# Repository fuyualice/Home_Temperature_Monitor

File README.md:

# BME280と電子ペーパーを使った自室の環境モニタリングデバイス

## 構成

- Bosh BME280
- Waveshare 4.2inch e-Paper Module
- ESP32-DevKitC-32E

## 仕様

- 10mごとにデータ取得
- データをInfluxDBに送信
- e-Paperの表示更新

- 毎日定時(0:00)にNTPから時刻同期

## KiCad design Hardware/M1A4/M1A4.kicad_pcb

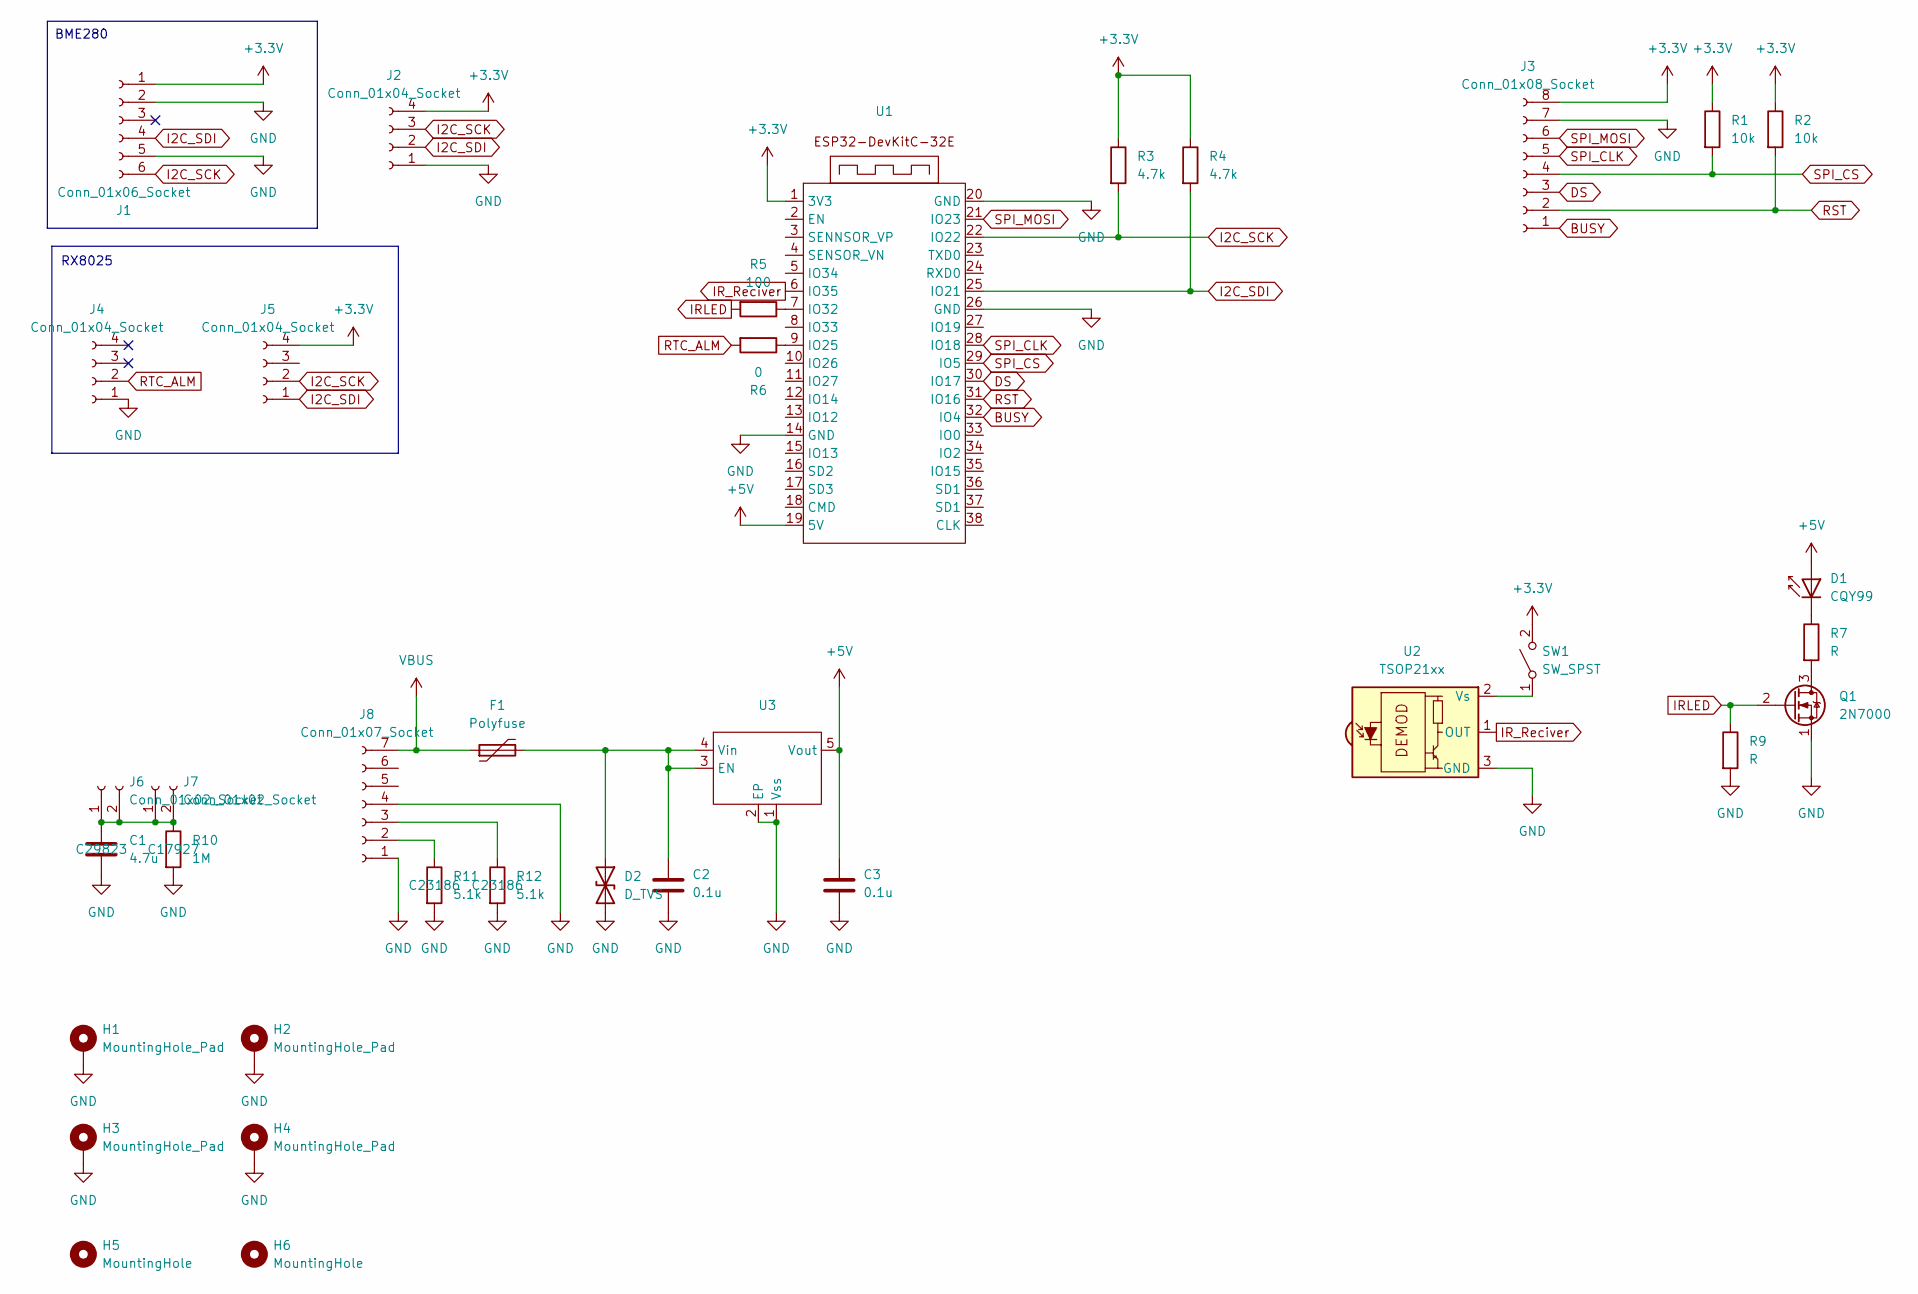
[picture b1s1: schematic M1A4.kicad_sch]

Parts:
C1: 4.7u; C_Disc_D4.3mm_W1.9mm_P5.00mm; LCSC C29823
C2, C3: 0.1u; C_Disc_D4.3mm_W1.9mm_P5.00mm
D1: CQY99; LED_D5.0mm_IRGrey
D2: D_TVS; D_DO-41_SOD81_P7.62mm_Horizontal
F1: Polyfuse; C_Disc_D10.5mm_W5.0mm_P5.00mm
H1, H2, H3, H4: MountingHole_Pad; MountingHole_3.2mm_M3_Pad_Via
H5, H6: MountingHole; MountingHole_3.2mm_M3
J1: Conn_01x06_Socket; PinHeader_1x06_P2.54mm_Vertical
J2: Conn_01x04_Socket; JST_XH_S4B-XH-A-1_1x04_P2.50mm_Horizontal
J3: Conn_01x08_Socket; JST_XH_S8B-XH-A_1x08_P2.50mm_Horizontal
J4, J5: Conn_01x04_Socket; PinHeader_1x04_P2.54mm_Vertical
J6, J7: Conn_01x02_Socket; PinHeader_1x02_P2.54mm_Vertical
J8: Conn_01x07_Socket; PinHeader_1x07_P2.54mm_Vertical
Q1: 2N7000; TO-92_Inline
R1, R2: 10k; R_Axial_DIN0207_L6.3mm_D2.5mm_P10.16mm_Horizontal
R3, R4: 4.7k; R_Axial_DIN0207_L6.3mm_D2.5mm_P10.16mm_Horizontal
R5: 100; R_Axial_DIN0207_L6.3mm_D2.5mm_P10.16mm_Horizontal
R6: 0; R_Axial_DIN0207_L6.3mm_D2.5mm_P10.16mm_Horizontal
R7, R9: R; R_Axial_DIN0207_L6.3mm_D2.5mm_P10.16mm_Horizontal
R10: 1M; R_Axial_DIN0207_L6.3mm_D2.5mm_P10.16mm_Horizontal; LCSC C17927
R11, R12: 5.1k; R_Axial_DIN0204_L3.6mm_D1.6mm_P5.08mm_Horizontal; LCSC C23186
SW1: SW_SPST
U1: esp32-devkit
U2: TSOP21xx; Vishay_MOLD-3Pin
U3: SOT-89-5_Handsoldering

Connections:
+3.3V: J1.1, J2.4, J3.8, J5.4, R1.1, R2.1, R3.1, R4.1, SW1.2 (B), U1.1 (3V3)
+5V: C3.1, D1.2 (A), U1.19 (5V), U3.5 (Vout)
BUSY: J3.1, U1.32 (IO4)
DS: J3.3, U1.30 (IO17)
GND: C1.2, C2.2, C3.2, D2.2 (A2), H1.1, H2.1, H3.1, H4.1, J1.2, J1.5, J2.1, J3.7, J4.1, J8.1, J8.4, Q1.1 (S), R9.2, R10.2, R11.2, R12.2, U1.14 (GND), U1.20 (GND), U1.26 (GND), U2.3 (GND), U3.1 (Vss), U3.2 (EP)
I2C_SCK: J1.6, J2.3, J5.2, R3.2, U1.22 (IO22)
I2C_SDI: J1.4, J2.2, J5.1, R4.2, U1.25 (IO21)
IRLED: Q1.2 (G), R5.2, R9.1
IR_Reciver: U1.6 (IO35), U2.1 (OUT)
unnamed: D1.1 (K), R7.1
unnamed: C2.1, D2.1 (A1), F1.2, U3.3 (EN), U3.4 (Vin)
unnamed: C1.1, J6.1, J6.2, J7.1, J7.2, R10.1
unnamed: J8.2, R11.1
unnamed: J8.3, R12.1
unnamed: Q1.3 (D), R7.2
unnamed: SW1.1 (A), U2.2 (Vs)
unnamed: R6.1, U1.9 (IO25)
unnamed: R5.1, U1.7 (IO32)
RST: J3.2, R2.2, U1.31 (IO16)
RTC_ALM: J4.2, R6.2
SPI_CLK: J3.5, U1.28 (IO18)
SPI_CS: J3.4, R1.2, U1.29 (IO5)
SPI_MOSI: J3.6, U1.21 (IO23)
VBUS: F1.1, J8.7

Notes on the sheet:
RX8025
BME280

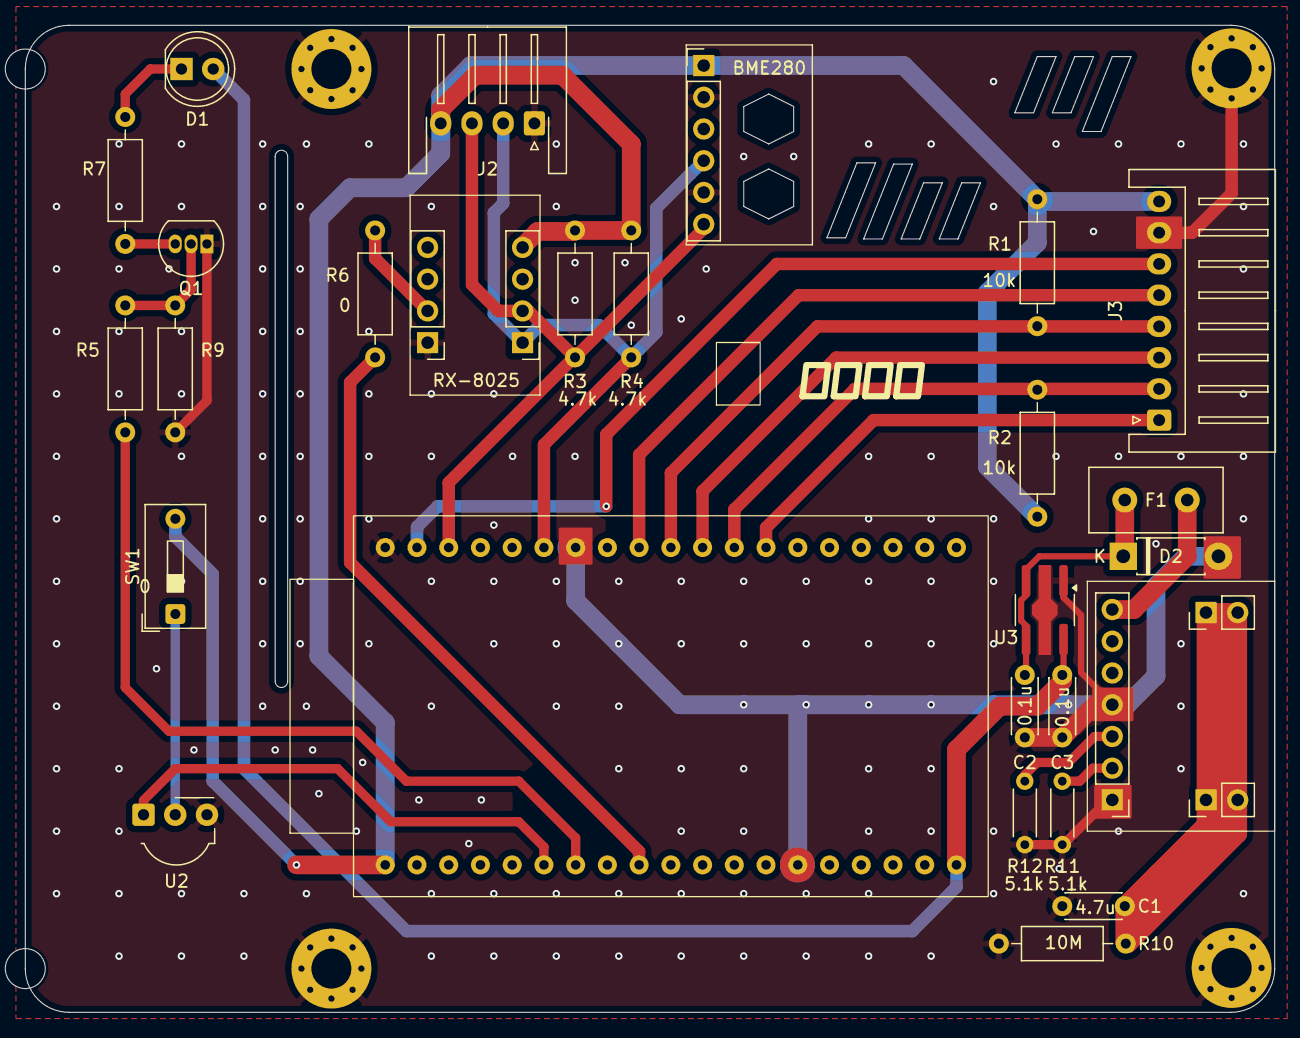
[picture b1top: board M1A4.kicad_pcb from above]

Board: 2 copper layers, 100.0 x 79.0 mm, 36 parts (0 on the bottom side), 24 nets.

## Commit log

2025-11-25 Home_Temperature_Monitor
2025-12-08 Fix: Resolve e-paper ghosting and position offset.
2025-12-11 Ignore assembly files.
2025-12-11 Update README.
2025-12-12 Fix: Resolve time drift issue after NTP sync.
